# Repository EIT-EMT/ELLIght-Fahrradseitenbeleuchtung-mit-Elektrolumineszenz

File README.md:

# 1 Fahrradseitenbeleuchtung mit Elektrolumineszenz

Dieses Projekt beinhaltet eine nachbaubare Lösung, um eine Seitenbeleuchtung an Fahrrädern mit Elektrolumineszenz zu realisieren. Zu dem Projekt gehören unter anderem ein SMD-Platinenlayout, ein Gehäuselayout und ein Programmcode [1]. Diese README stellt das Projekt vor. Die Datei [Anleitung](Anleitung.md) zeigt eine Möglichkeit, wie ein Nachbau des Ganzen erfolgen kann. Die benötigten Unterlagen sind mit angehängt. Jegliche Inhalte dieses Projektes unterliegen der CC BY-NC-SA 4.0 Lizenz.

# 2 Mehr Licht für mehr Sicherheit

Viele Fahrräder verfügen über einen Dynamo zur versorgung der klassischen Fahrradbeleuchtung. Zusätzliche Beleuchtung zu der klassischen Beleuchtung kann für mehr Sicherheit sorgen. Dieses Projekt realisiert eine solch zusätzliche Beleuchtung. Die entwickelte Schaltung greift Strom vom Dynamo ab, verarbeitet diesen und betreibt damit einen Treiber für Elektrolumineszenz (EL). Mit diesem lassen sich EL-Folien betreiben, welche sich z. B. beidseitig an der Fahrradgabel befestigen lassen. Die Abbildungen zeigen eine montierte EL-Folie (Abbildung 1) und den Einsatz dieser bei Nacht (Abbildung 2). Die Schaltung ist an eine alte Gesetzeslage angepasst, welches vorgab, dass die Nennspannung von Dynamos bzw. Lichtmaschinen bei 6 V und die Nennleistung bei 3 W liegt [2][3]. Bei hoher Geschwindigkeit und ausgeschalteter Front- und Heckbeleuchtung lassen sich jedoch abhängig vom Dynamo deutlich höhere Spannungswerte messen [2]. Zur Gewährleistung, dass dieses Projekt auch für den Einsatz am Fahrrad geeingt ist, sind verschiedene Tests durchgeführt worden. Diese Tests beruhen auf der Annahme, dass ein Fahrrad unter freiem Himmel im öffentlichen Straßenverkehr eingesetzt wird. Dabei kommt es zu Witterungseinflüssen und Unfällen. Erfolgt ein ordnungsgemäßer Aufbau, so kann dieser eine Schutzklasse von IP54 im gesamten Aufbau und IP 57 für die Platine erreichen. Dies bedeutet, dass Berührungschutz sichergestellt ist und ein Spritzwasserschutz bzw. für die Platine ein Schutz vor kurzzeitgem Untertauchen besteht. Außerdem ist der Aufbau für Temperaturen von minus 20°C bis plus 60°C einsetzbar. Der Aufbau von Platine und Gehäuse besitzt eine Schalgfertigkeitsklasse von IK07, so dass diese mindestens gegen Stütze aus zwei Meteren Höhe abgesichert sind. Grundsätzlich gilt, dass der gesamte Aufbau nach einem Sturz geprüft werden muss. Außerdem sollten nur Materialien verwendet werden, welche UV-beständig sind [4]. 

|| |
|----------|----------|
| Abbildung 1, Montierte EL-Folie [2]  | Abbildung 2, EL bei Nacht [2] |

##  2.1 Schaltplan/Platine

In der Abbildung 3 ist der Schaltplan dargestellt. Die weiteren Abbildungen 4 und 5 zeigen die 3D-Ansicht der dazugehörigen Platine. Die vom Dynamo kommende Wechselspannung wird zunächst mit vier Schottky-Dioden gleichgerichtet (D1 - D4). Um Spannungsstabilität zu gewährleisten, sind zwei Elektrolytkondensatoren verbaut [5]. In der Schaltung ist der Spannungsregler S13V10F5 des Herstellers Pololu verbaut. Dieser gibt eine Spannung von 5 V aus und funktioniert bei einer Eingangsspannung zwischen 2,8 V und maximal 22 V [6]. Die Ausgangsspannung von 5 V ist die Betriebsspannung der Schaltung [5]. Zum Schutz des Spannungsreglers ist ein Überspannungsschutz eingebaut. Bestehend aus Z-Diode, selbstsperrendem P-Kanal MOSFET und Lastwiderstand, greift dieser, sobald die Gesamtspannung die Gate-Soure-Spannung plus die Durchbruchspannung der Z-Diode übersteigt. Dies passiert bei ungefähr 12 V. In Tests zeigte sich, dass die Spannung selbst bei Geschwindigkeiten von bis zu 40 km/h nicht über 12,8 V am Spannungsregler ansteigt [2]. Außerdem sind zwei Schalter vorgesehen. Zum einen SW1, um die Schaltung ein- und auszuschalten und SW2, um die Betriebsart zu steuern. SW2 umfasst die Möglichkeit von einem Dauerlicht in einen Blinkmodus zu wechseln. Für die Lastwiderstände R2 und R3 ist es empfehlenswert, dass diese zusammen die Nennleistung von 3 W verbrauchen können [2]. Weitere Bauteile sind vorhanden, um eine Rückkopplung zu vermeiden und um den Betrieb der ICs zu ermöglichen [1][5]. Eine Verpolung der Schaltung innerhalb der einzelenen Kontaktstellen ist nicht möglich. 

||
|-------|
|Abbildung 3, Schaltplan, entnommen aus KiCad|

|||
|----------|----------|
|Abbildung 4, Platine, Seite Front, entnommen aus Kicad|Abbildung 5, Platine, Seite Back, entnommen aus KiCad |
         
## 2.2 Gehäuse 

Die Abbildungen 6, 7, 8 und 9 zeigen das Gehäuse aus der Vogelperspektive (Abbildung 6), seitlich von unten (Abbildung 7), aufgeschnitten (Abbildung 8) und als Drahtkörper (Abbildung 9). Es besteht aus zwei Teilen. Einem Deckel mit Durchführungen für die Schalter, welche jeweils mit EIN/AUS bzw. BLINKEN beschriftet sind. Außerdem ist der Schritzug ELLI(ght), welcher der Name des Projektes ist, auf dem Deckel mit versehen. Neben dem Deckel gibt es den Hauptkörper. Beide sind mittels einer glatten Ebene, einer Auflagefläche voneinander getrennt. Der Hauptkörper ist so geformt, dass sich dieser an einem Rohr mit 35 mm Durchmesser mittels Kabelbinder befestigen lässt. Bei Bedarf lässt sich der Körper an verschiedene Rohrdurchmesser anpassen. Dazu mehr unter "Gehäusenachbau" in der [Anleitung](Anleitung.md). Der Hauptkörper hat zwei Aussparungen für die Stromversorgung der Platine bzw. der EL-Folien. Diese sind so designt, dass sich Julet-Kabel so einschieben lassen, dass das Kabel durchgeführt wird und das der Stecker vom Kabel im Gehäuse verschwindet. Liegen beide Teile aufeinander, ergibt sich ein Hohlraum für die Platine. Dieser zieht sich durch beide Körper. Um den Hohlraum herum gibt es bei der Auflagefläche der Körper jeweils eine Aussparung für eine Dichtung. Diese Aussparungen ergeben zusammen einen Kreis mit einem Durchmesser von 2 mm. Außerdem sind Löcher für Senkkopfschrauben in dem Hauptkörper und Gewindeaufnahmen im Deckel vorgesehen, sodass sich die beiden Bauteile verschrauben lassen. Das Gehäuse hat eine Länge von 130,5 mm, eine maximale Breite von etwa 40,63 mm und in der für ein 35 mm Rohr vorgesehenen Ausführung eine Höhe von etwa 52,1 mm inklusive der Schrift.  

|| |
|--|--|
|Abbildung 6, Gehäuse, Vogelperspektive|Abbildung 7, Gehäuse, seitlich von unten|                                                                     
|||
|Abbildung 8, Gehäuse, aufgeschnitten| Abbildung 9, Gehäuse, Drahtkörper  |      

Abbildungen entnommen aus Autodesk Inventor

# 3 Literaturverzeichnis

[1] M. Schirmer (2025): „Entwicklung eines Fertigungsprozesses und Ansteuerungsoptimierung für elektrolumineszente Lacksysteme am Beispiel einer Fahrradseitenbeleuchtung“, Bachelorarbeit, Hochschule Hannover

[2] A. Hesse (2024): „Realisierung einer elektrolumineszierenden Fahrradseitenbeleuchtung“, Bachelorarbeit, Hochschule Hannover

[3] buzer.de: "Änderung § 67 StVZO vom 01.06.2017", Zugriff am 09.12.2025. [Online.] https://www.buzer.de/gesetz/10146/al61160-0.htm 

[4] Conrad Electronic SE (2025). „IP Schutzklassen und Schutzarten“,  Zugriff am 09.12.2025 [Online.] https://www.conrad.de/de/ratgeber/industrie-40/ip-schutzklassen-und-schutzarten.html 

[5] T. Kollmeier (2024): „Elektrolumineszenz-basierte Seitenbeleuchtung für Fahrräder“, Masterarbeit, Hochschule Hannover

[6] Pololu: "5V, 1A Step-Up/Step-Down Voltage Regulator S13V10F5", Zugriff am 09.12.2025. [Online.] https://www.pololu.com/product-info-merged/4083

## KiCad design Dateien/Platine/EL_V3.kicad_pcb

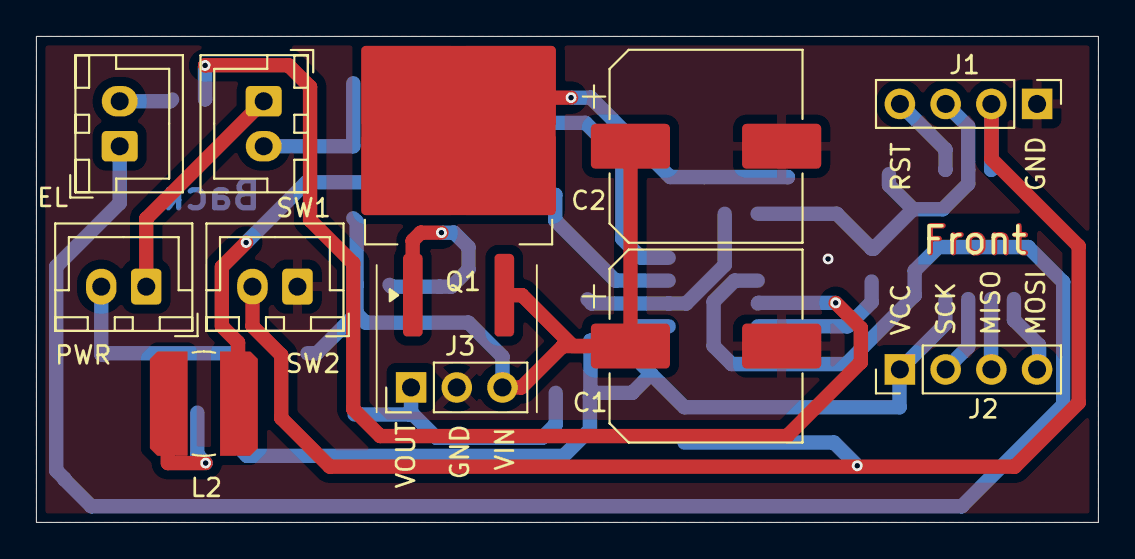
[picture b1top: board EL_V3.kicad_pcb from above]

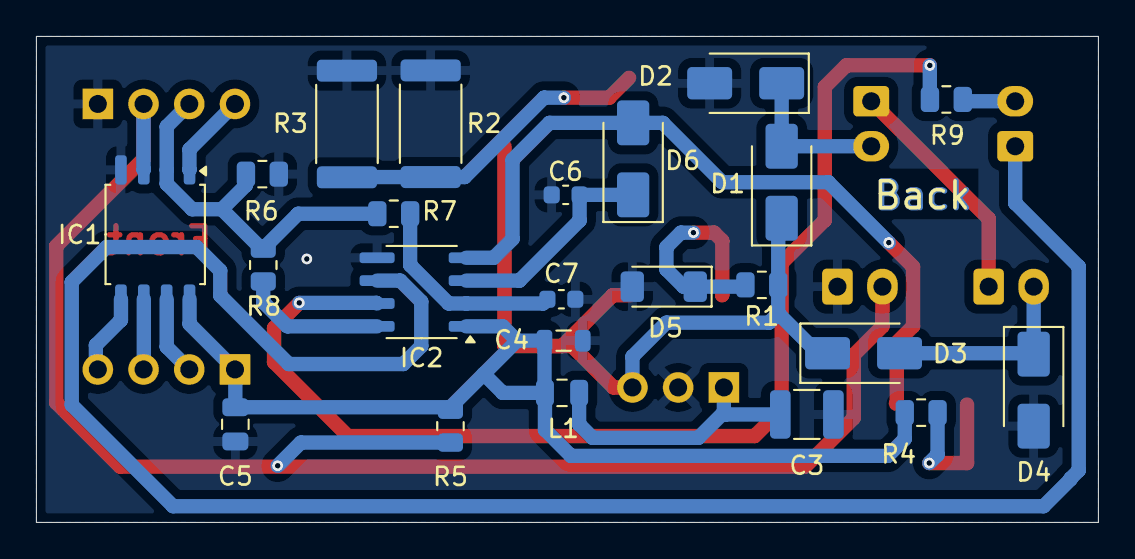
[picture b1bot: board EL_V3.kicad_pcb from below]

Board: 2 copper layers, 59.0 x 27.0 mm, 34 parts (23 on the bottom side), 23 nets.

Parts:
C1, C2: 470 µF 35V; CP_Elec_10x10.5
C3: 4,7 µF 16V; C_1210_3225Metric
C4: 0,1 µF 16V; L_0805_2012Metric
C5: 1000 nF; C_0805_2012Metric
C6: 10 nF 250V; C_0603_1608Metric
C7: 1 nF; C_0603_1608Metric
D1, D2, D3, D4: VS-10MQ040-M3; D_SMA
D5: BZV55B10; D_MiniMELF
D6: BAS21; D_SMA
EL: Conn_01x02_Pin; JST_XH_B2B-XH-A_1x02_P2.50mm_Vertical
IC1: ATtiny85V-10S; SOIC-8_5.3x5.3mm_P1.27mm
IC2: HV830LG-G; SOIC-8_3.9x4.9mm_P1.27mm
J1, J2: Conn_01x04_Pin; PinHeader_1x04_P2.54mm_Vertical
J3: Conn_01x03_Pin; PinHeader_1x03_P2.54mm_Vertical
L1: 10 µH; C_0805_2012Metric
L2: 220 µH; L_Bourns_SDR0604
PWR: Conn_01x02_Pin; JST_XH_B2B-XH-A_1x02_P2.50mm_Vertical
Q1: IRF4905; TO-263-2
R1, R5, R6: 10k; R_0805_2012Metric
R2, R3: 30; R_2512_6332Metric
R4: 8,2; R_0805_2012Metric
R7: 1M; R_0805_2012Metric
R8: 3,3M; R_0805_2012Metric
R9: 1k; R_0805_2012Metric
SW1: On/ OFF; JST_XH_B2B-XH-A_1x02_P2.50mm_Vertical
SW2: Blink/ Steady; JST_XH_B2B-XH-A_1x02_P2.50mm_Vertical

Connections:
+6V: PWR.1, SW1.1 (A)
-6V: D3.2 (A), D4.1 (K), PWR.2
GND: C1.2, C2.2, C3.2, C4.2, C5.1, C6.2, C7.2, D2.2 (A), D4.2 (A), D5.2 (A), IC1.4 (GND), IC2.5 (GND), J1.1, J3.2, R2.2, R3.2, R6.1, SW2.1 (A)
unnamed: D1.2 (A), D2.1 (K), SW1.2 (B)
unnamed: C1.1, C2.1, D1.1 (K), D3.1 (K), J3.3, Q1.3 (S), R1.1
unnamed: D5.1 (K), Q1.1 (G), R1.2
unnamed: D6.2 (A), IC2.4 (LX), L2.2
unnamed: C6.1, D6.1 (K), IC2.3 (CS)
unnamed: C4.1, C5.2, IC1.8 (VCC), IC2.1 (VDD), J2.1, L1.1, R4.1, R5.1
unnamed: IC1.7 (PB2), J2.2
unnamed: IC1.6 (PB1), J2.3
unnamed: IC1.5 (AREF/PB0), J2.4
unnamed: C3.1, J3.1, L1.2
unnamed: IC1.3 (XTAL2/PB4), J1.2, R5.2, SW2.2 (B)
unnamed: IC1.2 (XTAL1/PB3), J1.3, R6.2, R7.1, R8.1
unnamed: IC1.1 (~RESET/PB5), J1.4
unnamed: EL.1, IC2.6 (VB)
unnamed: EL.2, R9.1
unnamed: L2.1, R4.2
unnamed: Q1.2 (D), R2.1, R3.1
unnamed: C7.1, IC2.2 (RSW-Osc), R7.2
unnamed: IC2.8 (Rel-Osc), R8.2
unnamed: IC2.7 (VA), R9.2

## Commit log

2026-01-05 Dateien
2026-01-05 Neue Datei
2026-01-06 Fix section numbering and enhance README content
    Updated the README to correct section numbering and improve clarity.
